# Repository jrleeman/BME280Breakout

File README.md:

# BME280 Breakout

## Purpose

Breakout board for the Bosch BME280 sensor. Selectable address and optional
pull-up resistors. This looks like a great little sensor and we wanted to
try it out!

## Purchasing

The dual channel instrumentation amplifier is available through Leeman
Geophysical by emailing [John R. Leeman](http://www.johnrleeman.com) at
<kd5wxb@gmail.com>.

## Project Information

This repository includes all design information, CAD files, PDF CAD output,
gerbers, etc.

Additional resources for this project include:

- [BME280 Datasheet](PDFs/bme280.pdf)
- [Bosch Drive Code Repo (from Bosch)](https://github.com/BoschSensortec/BME280_driver)
- [Example Arduino Code (from Embedded Adventures)](https://github.com/embeddedadventures/BME280)

## License

This product is licensed under the CERN Open Hardware License 1.2. The [full
license](cern_ohl_v_1_2.txt) is included in this repository.

## Hookup Guide

Connect the sensor to a 3.3 VDC supply and ground. Connect to the I2C bus of
your micro-controller or system. Note that this unit is NOT 5 VDC tolerant!
If you are using 5 VDC logic, please use a [level shifter](https://www.sparkfun.com/products/12009?gclid=CJTokbvrusUCFegF7AodUhAAqw) to prevent damage.

## Example Data

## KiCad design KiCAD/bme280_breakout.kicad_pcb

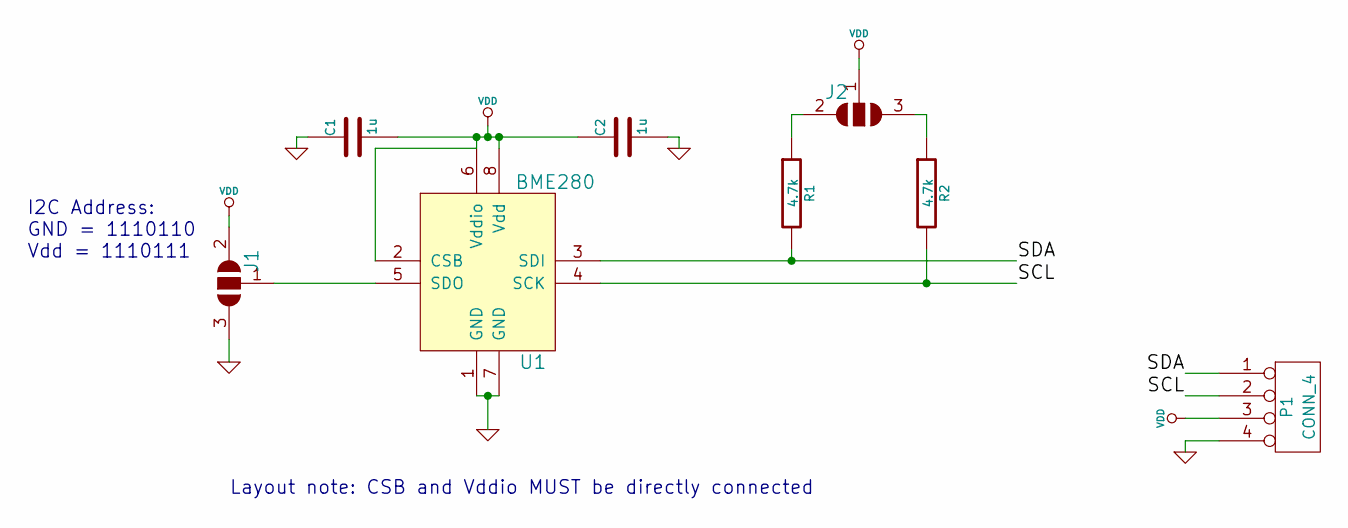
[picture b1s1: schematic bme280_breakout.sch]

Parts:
C1, C2: 1u
J1, J2: 2JUMPER
P1: CONN_4
R1, R2: 4.7k
U1: BME280

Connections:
/SCL: P1.2, R2.2, U1.4 (SCK)
/SDA: P1.1, R1.2, U1.3 (SDI)
GND: C1.1, C2.2, J1.3, P1.4, U1.1 (GND), U1.7 (GND)
unnamed: J2.2, R1.1
unnamed: J2.3, R2.1
unnamed: J1.1, U1.5 (SDO)
VDD: C1.2, C2.1, J1.2, J2.1, P1.3, U1.2 (CSB), U1.6 (Vddio), U1.8 (Vdd)

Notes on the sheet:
I2C Address: GND = 1110110 Vdd = 1110111
Layout note: CSB and Vddio MUST be directly connected

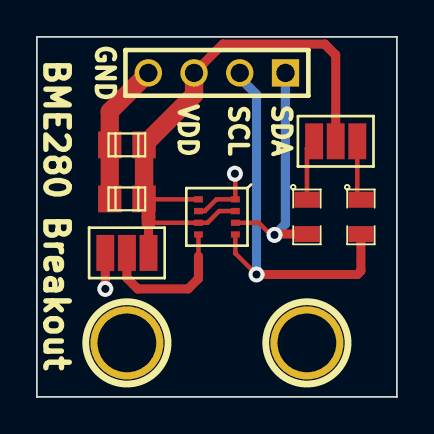
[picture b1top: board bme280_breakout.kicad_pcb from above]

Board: 2 copper layers, 20.0 x 20.0 mm, 10 parts (0 on the bottom side), 7 nets.

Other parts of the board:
1PIN, 1PIN#2: P***; 1pin

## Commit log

2015-04-15 Add datasheet
2015-05-11 Update documentation and clean up repo
2015-05-11 Add example data plot
